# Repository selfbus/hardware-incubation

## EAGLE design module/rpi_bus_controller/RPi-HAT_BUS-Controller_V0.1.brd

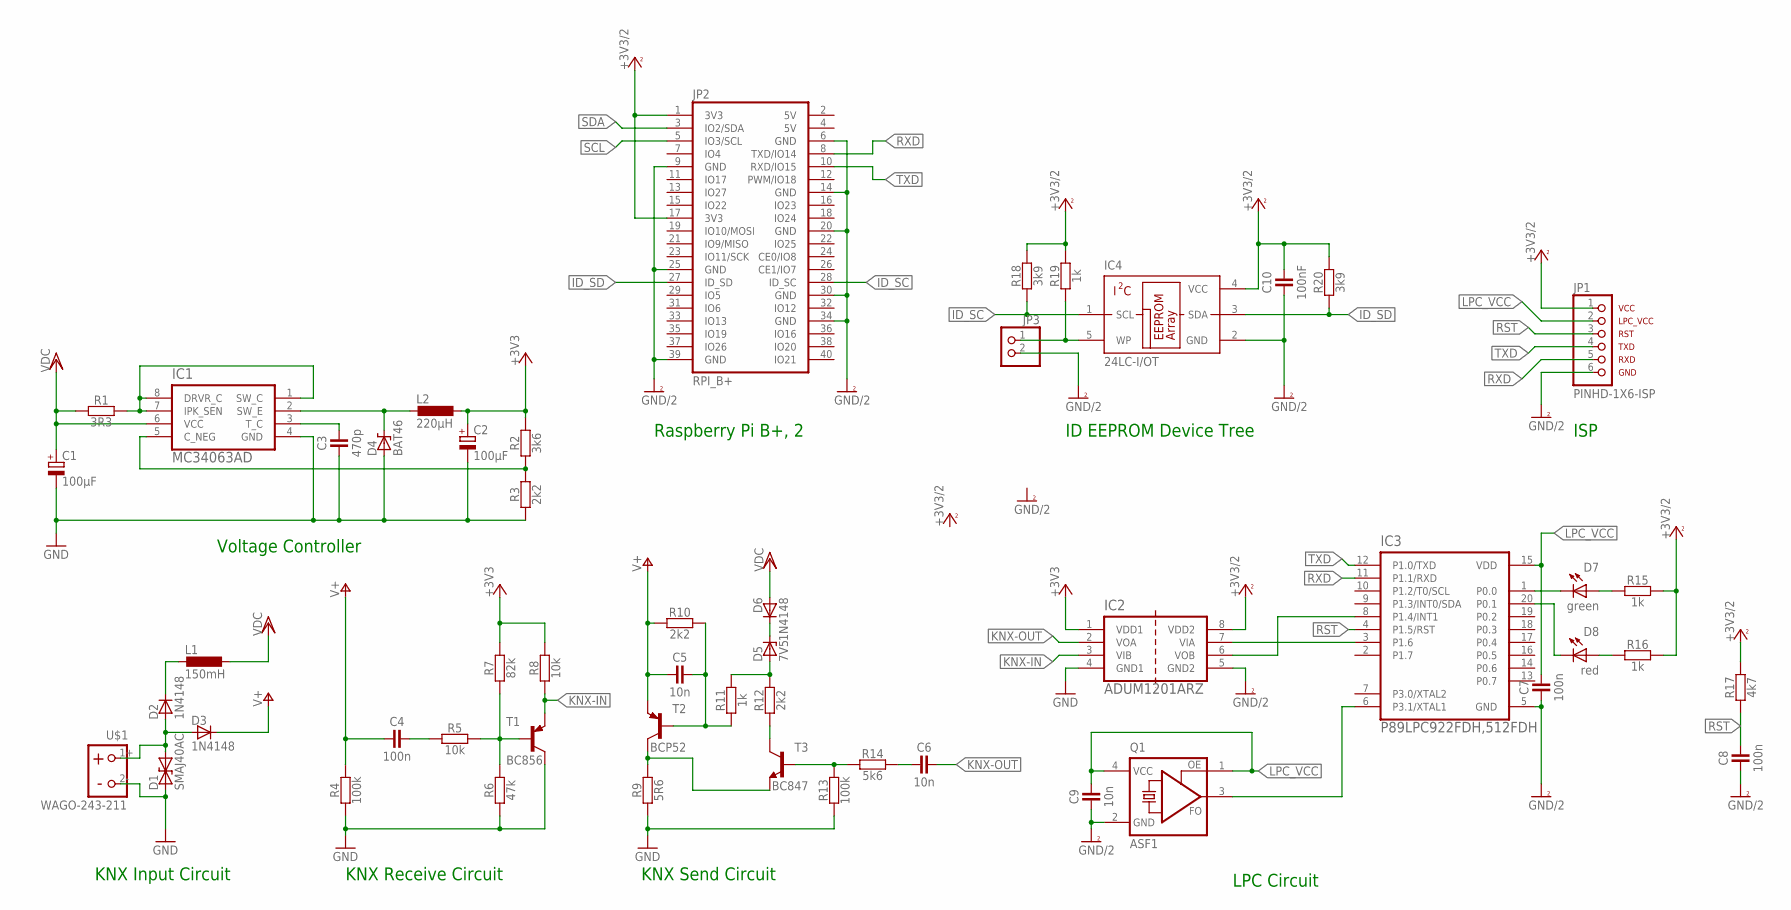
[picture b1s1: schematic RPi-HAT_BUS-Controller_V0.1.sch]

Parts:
C1: 100µF; PANASONIC_D
C2: 100µF; PANASONIC_C
C3: 470p; R1206
C4, C7, C8: 100n; R1206
C5, C6, C9: 10n; R1206
C10: 100nF; R1206
D1: SMAJ40AC; DO-214AC
D2, D3, D6: 1N4148; MINIMELF
D4: BAT46; MINIMELF
D5: 7V5; MINIMELF
D7: green; CHIPLED_1206
D8: red; CHIPLED_1206
IC1: MC34063AD; SOIC127P600X175-8N
IC2: ADUM1201ARZ; SOIC127P600X175-8N
IC3: P89LPC922FDH,512FDH; SOP65P640X110-20N
IC4: 24LC-I/OT; SOT23-5
JP1: PINHD-1X6-ISP; 1X06
JP2: RPI_B+; RPI-B+HAT
JP3: PINHD-1X2; 1X02
L1: 150mH; 11P-L1
L2: 220µH; 2200-11.43
Q1: ASF1; ASF
R1: 3R3; R1206
R2: 3k6; R1206
R3, R10, R12: 2k2; R1206
R4, R13: 100k; R1206
R5, R8: 10k; R1206
R6: 47k; R1206
R7: 82k; R1206
R9: 5R6; R1206
R11, R15, R16, R19: 1k; R1206
R14: 5k6; R1206
R17: 4k7; R1206
R18, R20: 3k9; R1206
T1: BC856; SOT23
T2: BCP52; SOT223
T3: BC847; SOT23
U$1: WAGO-243-211

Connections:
+3V3: C2.+, IC2.1 (VDD1), L2.1, R2.2, R7.2, R8.2
+3V3/2: C10.2, IC2.8 (VDD2), IC4.4 (VCC), JP1.1, JP2.1 (3V3), JP2.17 (3V3), R15.2, R16.2, R17.2, R18.2, R19.2, R20.2
GND: C1.-, C2.-, C3.1, D1.A, D4.A, IC1.4 (GND), IC2.4 (GND1), R3.1, R4.1, R6.1, R9.1, R13.1, T1.3 (C), U$1.2-
GND/2: C7.1, C8.1, C9.1, C10.1, IC2.5 (GND2), IC3.5 (GND), IC4.2 (GND), JP1.6, JP2.6 (GND), JP2.9 (GND), JP2.14 (GND), JP2.20 (GND), JP2.25 (GND), JP2.30 (GND), JP2.34 (GND), JP2.39 (GND), JP3.2, Q1.2 (GND)
ID_SC: IC4.1 (SCL), JP2.28 (ID_SC), R18.1
ID_SD: IC4.3 (SDA), JP2.27 (ID_SD), R20.1
KNX-IN: IC2.3 (VIB), R8.1, T1.2 (E)
KNX-OUT: C6.2, IC2.2 (VOA)
LPC_VCC: C7.2, C9.2, IC3.15 (VDD), JP1.2, Q1.1 (OE), Q1.4 (VCC)
unnamed: D1.C, D2.A, D3.A, U$1.1+
unnamed: IC1.5 (C_NEG), R2.1, R3.2
unnamed: C4.2, R5.1
unnamed: D2.C, L1.2
unnamed: R5.2, R6.2, R7.1, T1.1 (B)
unnamed: IC1.1 (SW_C), IC1.7 (IPK_SEN), IC1.8 (DRVR_C), R1.2
unnamed: C3.2, IC1.3 (T_C)
unnamed: IC4.5 (WP), JP3.1, R19.1
unnamed: D4.C, IC1.2 (SW_E), L2.2
unnamed: IC2.7 (VIA), IC3.3 (P1.6)
unnamed: R9.2, T2.2 (C), T2.4 (C), T3.2 (E)
unnamed: C5.2, R10.2, R11.1, T2.1 (B)
unnamed: D5.A, R11.2, R12.2
unnamed: R12.1, T3.3 (C)
unnamed: R13.2, R14.1, T3.1 (B)
unnamed: C6.1, R14.2
unnamed: D5.C, D6.C
unnamed: IC3.6 (P3.1/XTAL1), Q1.3 (FO)
unnamed: IC2.6 (VOB), IC3.8 (P1.4/INT1)
unnamed: D7.C, IC3.1 (P0.0)
unnamed: D7.A, R15.1
unnamed: D8.C, IC3.20 (P0.1)
unnamed: D8.A, R16.1
RST: C8.2, IC3.4 (P1.5/RST), JP1.3, R17.1
RXD: IC3.11 (P1.1/RXD), JP1.5, JP2.8 (TXD/IO14)
SCL: JP2.5 (IO3/SCL)
SDA: JP2.3 (IO2/SDA)
TXD: IC3.12 (P1.0/TXD), JP1.4, JP2.10 (RXD/IO15)
V+: C4.1, C5.1, D3.C, R4.2, R10.1, T2.3 (E)
VDD: C1.+, D6.A, IC1.6 (VCC), L1.1, R1.1

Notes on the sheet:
KNX Input Circuit
Voltage Controller
KNX Receive Circuit
KNX Send Circuit
Raspberry Pi B+, 2
ISP
LPC Circuit
ID EEPROM Device Tree

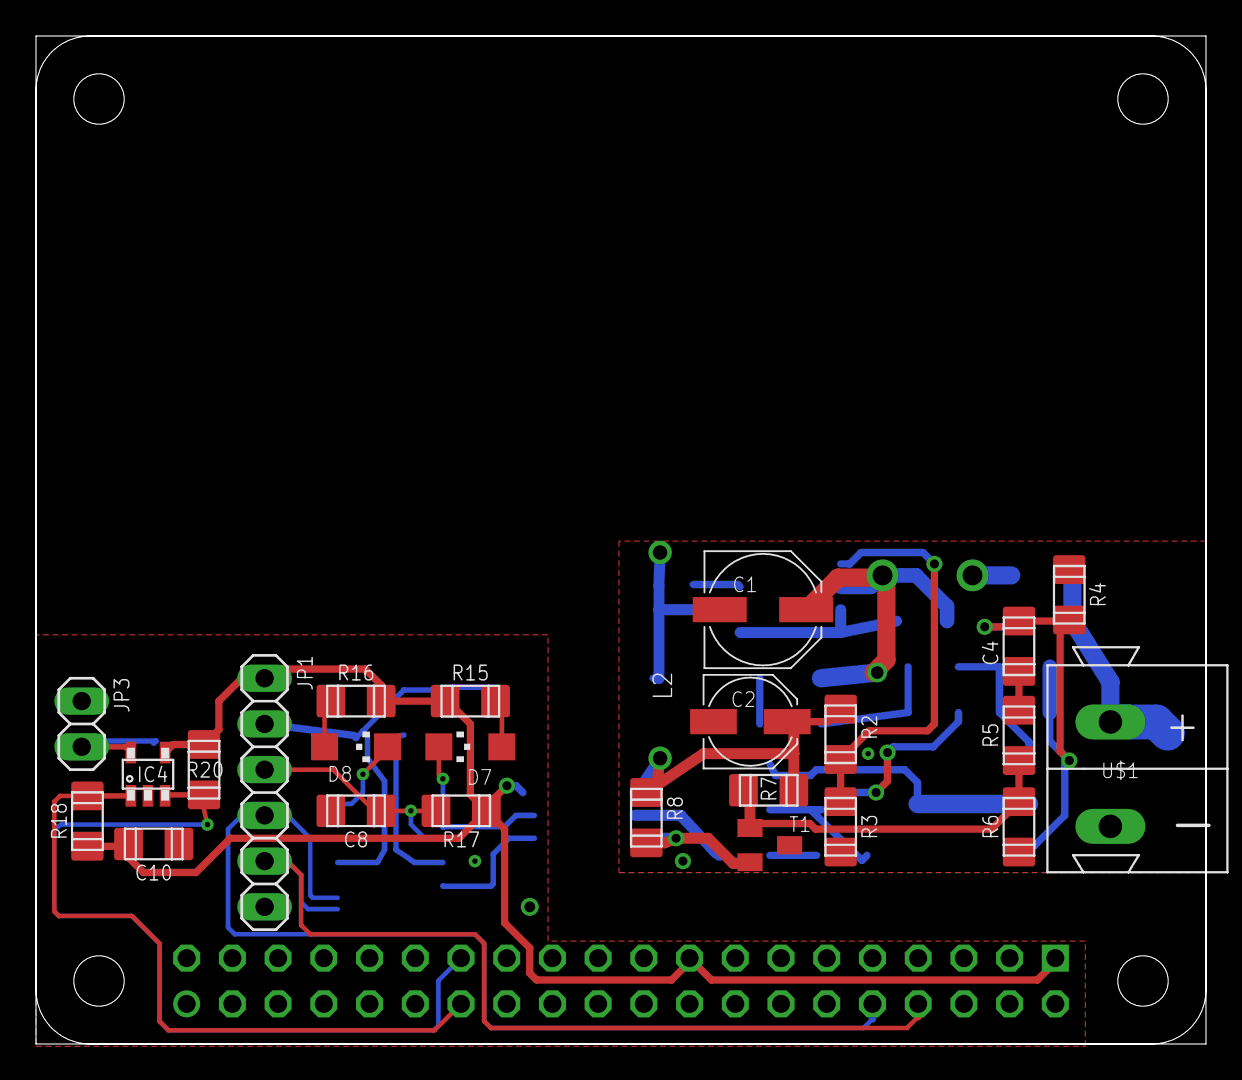
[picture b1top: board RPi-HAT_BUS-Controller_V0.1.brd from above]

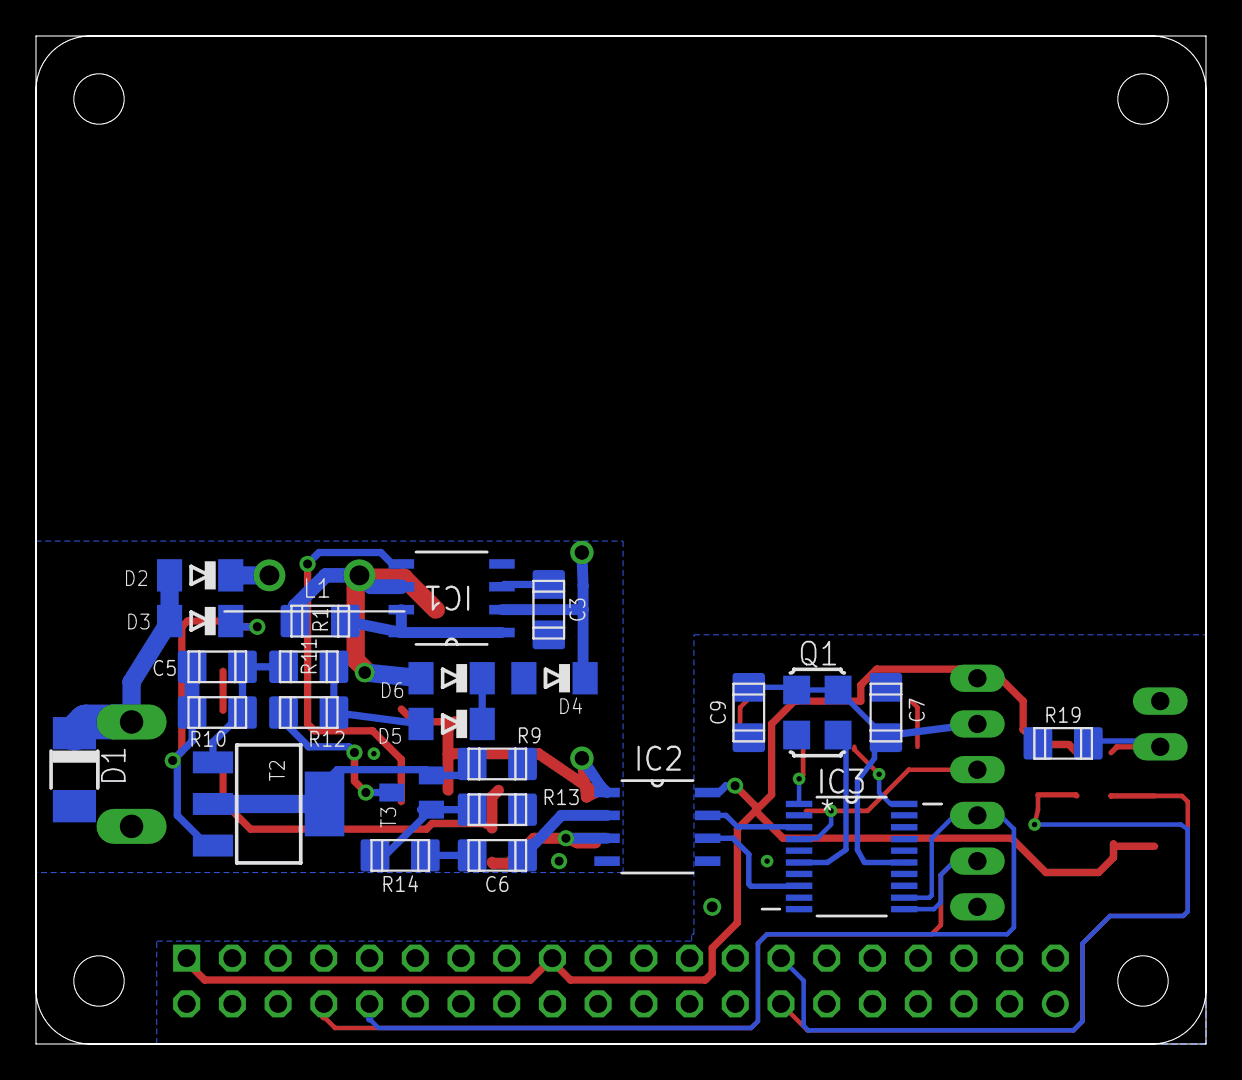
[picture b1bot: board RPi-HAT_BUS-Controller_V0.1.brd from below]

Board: 2 copper layers, 65.0 x 56.0 mm, 52 parts (26 on the bottom side), 37 nets.
